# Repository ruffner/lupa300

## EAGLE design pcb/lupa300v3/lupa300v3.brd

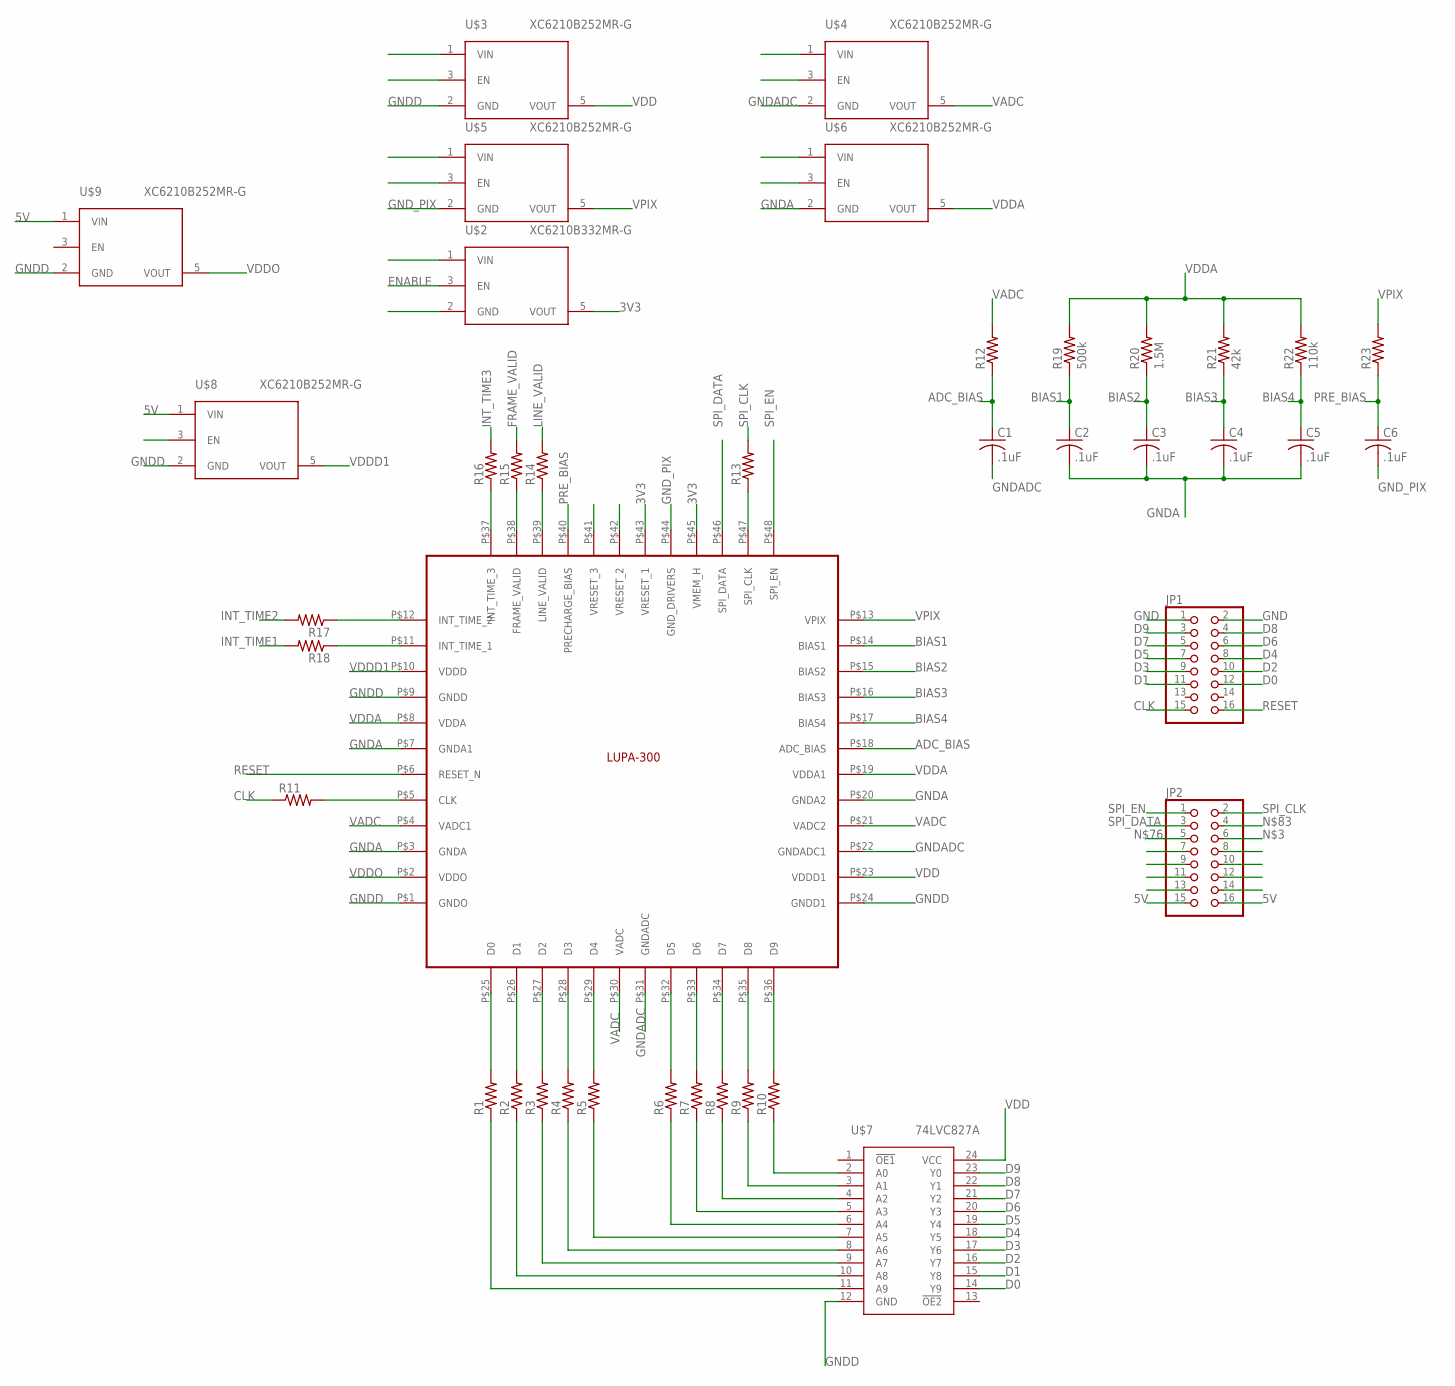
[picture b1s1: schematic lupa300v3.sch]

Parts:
C1, C2, C3, C4, C5, C6: .1uF; C0603K
JP1, JP2: PINHD-2X8; 2X08
R1, R2, R3, R4, R5, R6, R7, R8, R9, R10, R11, R12, R13, R14, R15, R16, R17, R18, R23: R-US_R0603; R0603
R19: 500k; R0603
R20: 1.5M; R0603
R21: 42k; R0603
R22: 110k; R0603
U$1: LUPA300
U$2: XC6210B332MR-G; SOT25
U$3, U$4, U$5, U$6, U$8, U$9: XC6210B252MR-G; SOT25
U$7: 74LVC827A; TSSOP24

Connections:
3V3: U$1.P$43 (VRESET_1), U$1.P$45 (VMEM_H), U$2.5 (VOUT)
5V: JP2.15, JP2.16, U$2.1 (VIN), U$3.1 (VIN), U$4.1 (VIN), U$5.1 (VIN), U$6.1 (VIN), U$8.1 (VIN), U$9.1 (VIN)
ADC_BIAS: C1.1, R12.1, U$1.P$18 (ADC_BIAS)
BIAS1: C2.1, R19.1, U$1.P$14 (BIAS1)
BIAS2: C3.1, R20.1, U$1.P$15 (BIAS2)
BIAS3: C4.1, R21.1, U$1.P$16 (BIAS3)
BIAS4: C5.1, R22.1, U$1.P$17 (BIAS4)
CLK: JP1.15, R11.1
D0: JP1.12, U$7.14 (Y9)
D1: JP1.11, U$7.15 (Y8)
D2: JP1.10, U$7.16 (Y7)
D3: JP1.9, U$7.17 (Y6)
D4: JP1.8, U$7.18 (Y5)
D5: JP1.7, U$7.19 (Y4)
D6: JP1.6, U$7.20 (Y3)
D7: JP1.5, U$7.21 (Y2)
D8: JP1.4, U$7.22 (Y1)
D9: JP1.3, U$7.23 (Y0)
ENABLE: U$2.3 (EN), U$3.3 (EN), U$4.3 (EN), U$5.3 (EN), U$6.3 (EN)
FRAME_VALID: R15.2
GND: JP1.1, JP1.2
GNDA: C2.2, C3.2, C4.2, C5.2, U$1.P$3 (GNDA), U$1.P$7 (GNDA1), U$1.P$20 (GNDA2), U$6.2 (GND)
GNDADC: C1.2, U$1.P$22 (GNDADC1), U$1.P$31 (GNDADC), U$4.2 (GND)
GNDD: U$1.P$1 (GNDO), U$1.P$9 (GNDD), U$1.P$24 (GNDD1), U$3.2 (GND), U$7.12 (GND), U$8.2 (GND), U$9.2 (GND)
GND_PIX: C6.2, U$1.P$44 (GND_DRIVERS), U$5.2 (GND)
INT1: R18.1, U$1.P$11 (INT_TIME_1)
INT2: R17.1, U$1.P$12 (INT_TIME_2)
INT_TIME1: R18.2
INT_TIME2: R17.2
INT_TIME3: R16.2
LINE_VALID: R14.2
unnamed: R1.2, U$1.P$25 (D0)
unnamed: R2.2, U$1.P$26 (D1)
unnamed: R3.2, U$1.P$27 (D2)
unnamed: R4.2, U$1.P$28 (D3)
unnamed: R5.2, U$1.P$29 (D4)
unnamed: R6.2, U$1.P$32 (D5)
unnamed: R7.2, U$1.P$33 (D6)
unnamed: R8.2, U$1.P$34 (D7)
unnamed: R9.2, U$1.P$35 (D8)
unnamed: R10.2, U$1.P$36 (D9)
unnamed: R11.2, U$1.P$5 (CLK)
unnamed: R13.1, U$1.P$47 (SPI_CLK)
unnamed: R14.1, U$1.P$39 (LINE_VALID)
unnamed: R15.1, U$1.P$38 (FRAME_VALID)
unnamed: R16.1, U$1.P$37 (INT_TIME_3)
unnamed: R10.1, U$7.2 (A0)
unnamed: R9.1, U$7.3 (A1)
unnamed: R8.1, U$7.4 (A2)
unnamed: R7.1, U$7.5 (A3)
unnamed: R6.1, U$7.6 (A4)
unnamed: R5.1, U$7.7 (A5)
unnamed: R4.1, U$7.8 (A6)
unnamed: R3.1, U$7.9 (A7)
unnamed: R2.1, U$7.10 (A8)
unnamed: R1.1, U$7.11 (A9)
PRE_BIAS: C6.1, R23.1, U$1.P$40 (PRECHARGE_BIAS)
RESET: JP1.16, U$1.P$6 (RESET_N)
SPI_CLK: JP2.2, R13.2
SPI_DATA: JP2.3, U$1.P$46 (SPI_DATA)
SPI_EN: JP2.1, U$1.P$48 (SPI_EN)
VADC: R12.2, U$1.P$4 (VADC1), U$1.P$21 (VADC2), U$1.P$30 (VADC), U$4.5 (VOUT)
VDD: U$1.P$23 (VDDD1), U$3.5 (VOUT), U$7.24 (VCC)
VDDA: R19.2, R20.2, R21.2, R22.2, U$1.P$8 (VDDA), U$1.P$19 (VDDA1), U$6.5 (VOUT)
VDDD1: U$1.P$10 (VDDD), U$8.5 (VOUT)
VDDO: U$1.P$2 (VDDO), U$9.5 (VOUT)
VPIX: R23.2, U$1.P$13 (VPIX), U$5.5 (VOUT)

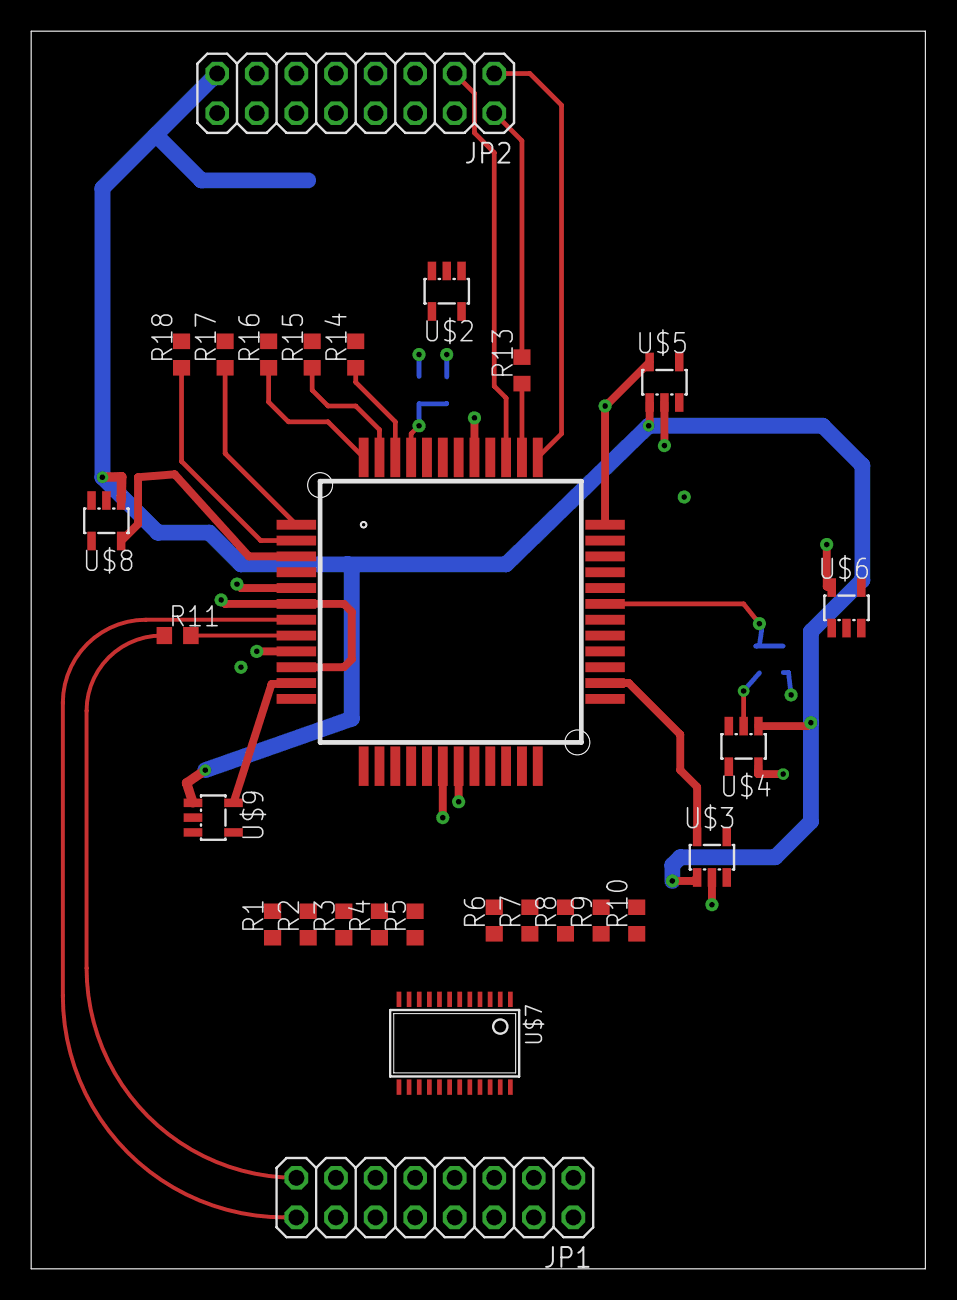
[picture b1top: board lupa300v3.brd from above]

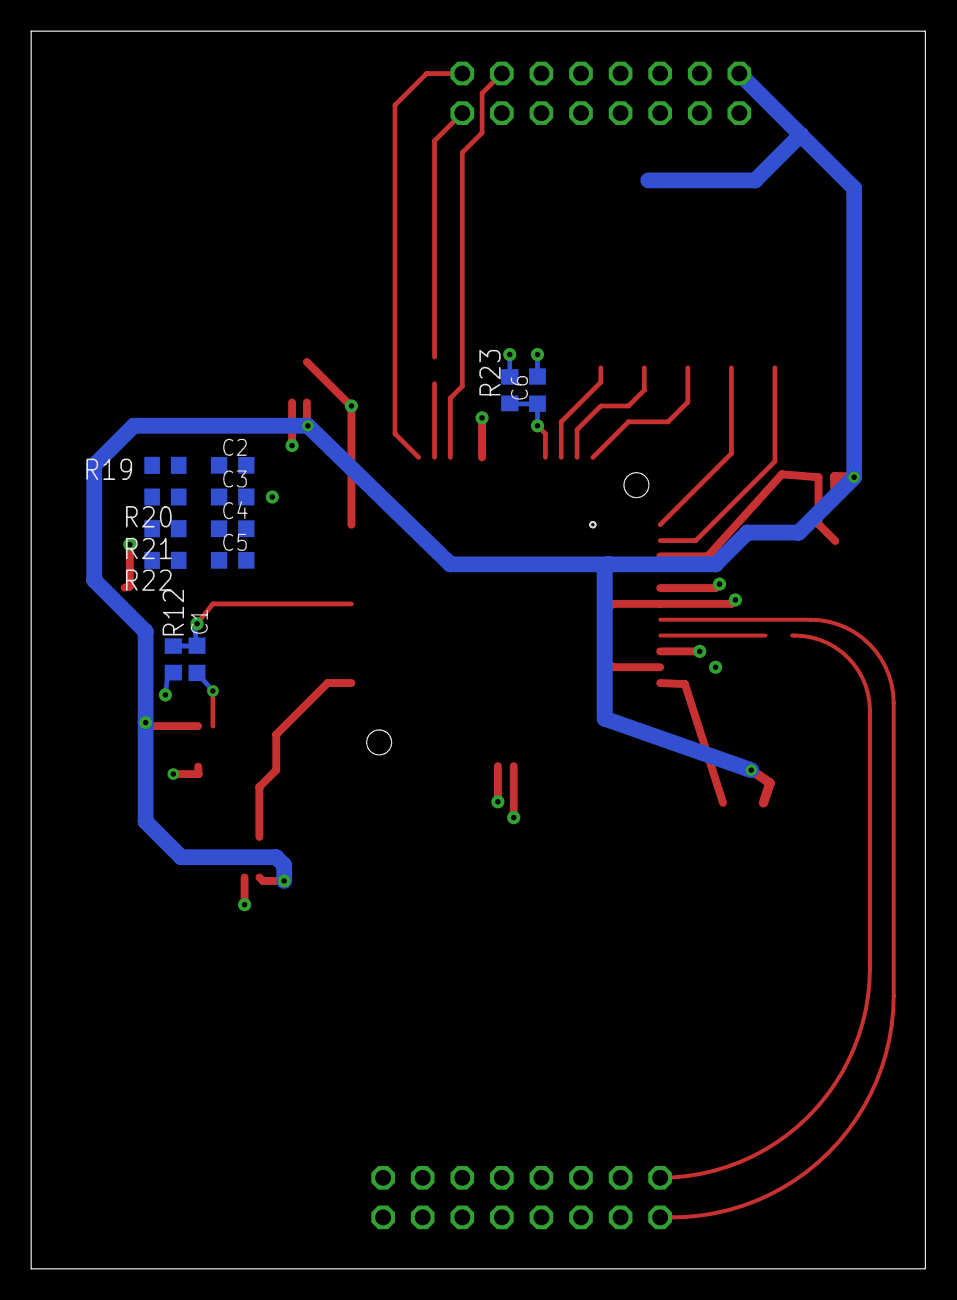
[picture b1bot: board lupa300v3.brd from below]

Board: 4 copper layers, 57.4 x 79.4 mm, 40 parts (12 on the bottom side), 62 nets.

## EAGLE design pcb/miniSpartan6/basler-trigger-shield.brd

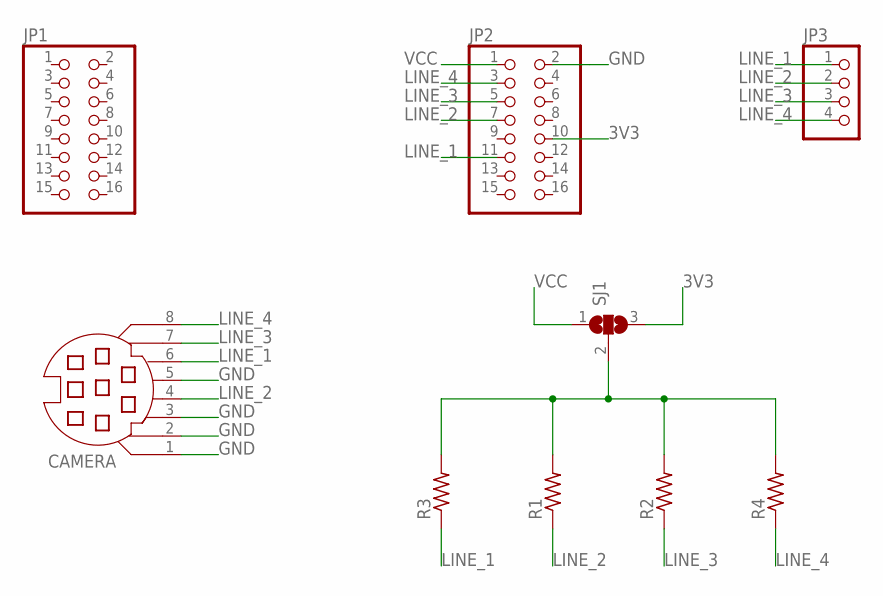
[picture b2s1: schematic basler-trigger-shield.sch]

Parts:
CAMERA: MD08SS; MDIN08SS
JP1, JP2: PINHD-2X8; 2X08
JP3: PINHD-1X4; 1X04
R1, R2, R3, R4: R-US_R0603; R0603
SJ1: SJ2W; SJ_2

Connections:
3V3: JP2.10, SJ1.3
GND: CAMERA.1, CAMERA.2, CAMERA.3, CAMERA.5, JP2.2
LINE_1: CAMERA.6, JP2.11, JP3.1, R3.1
LINE_2: CAMERA.4, JP2.7, JP3.2, R1.1
LINE_3: CAMERA.7, JP2.5, JP3.3, R2.1
LINE_4: CAMERA.8, JP2.3, JP3.4, R4.1
unnamed: R1.2, R2.2, R3.2, R4.2, SJ1.2
VCC: JP2.1, SJ1.1

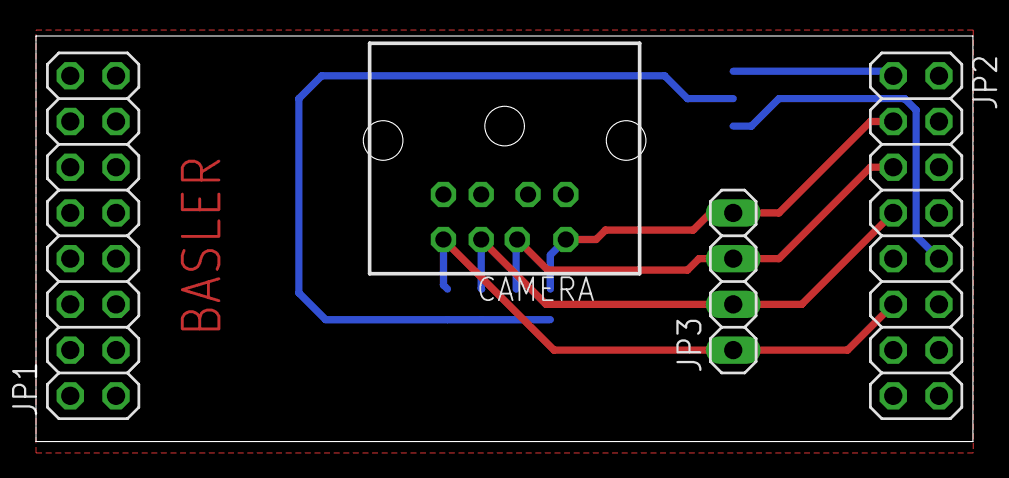
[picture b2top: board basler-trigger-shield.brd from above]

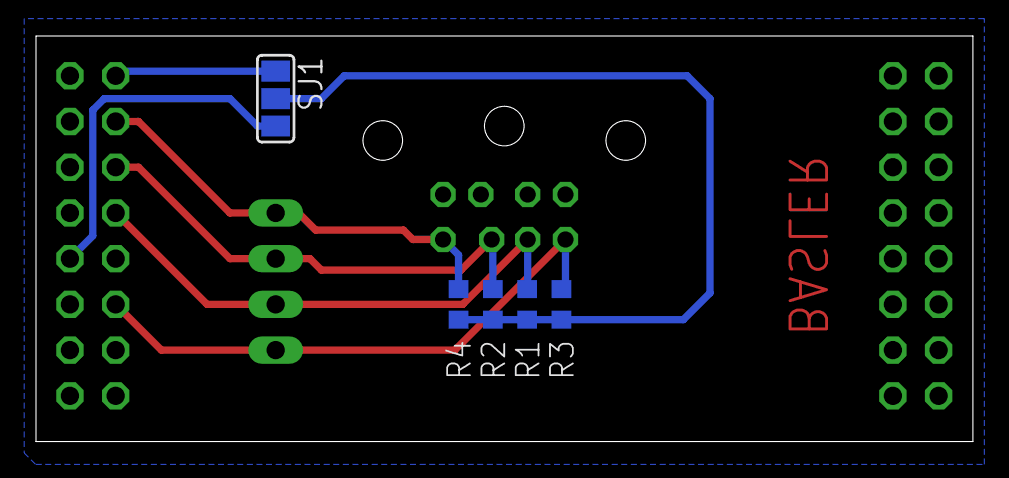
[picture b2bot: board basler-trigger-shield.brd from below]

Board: 2 copper layers, 52.0 x 22.5 mm, 9 parts (5 on the bottom side), 8 nets.

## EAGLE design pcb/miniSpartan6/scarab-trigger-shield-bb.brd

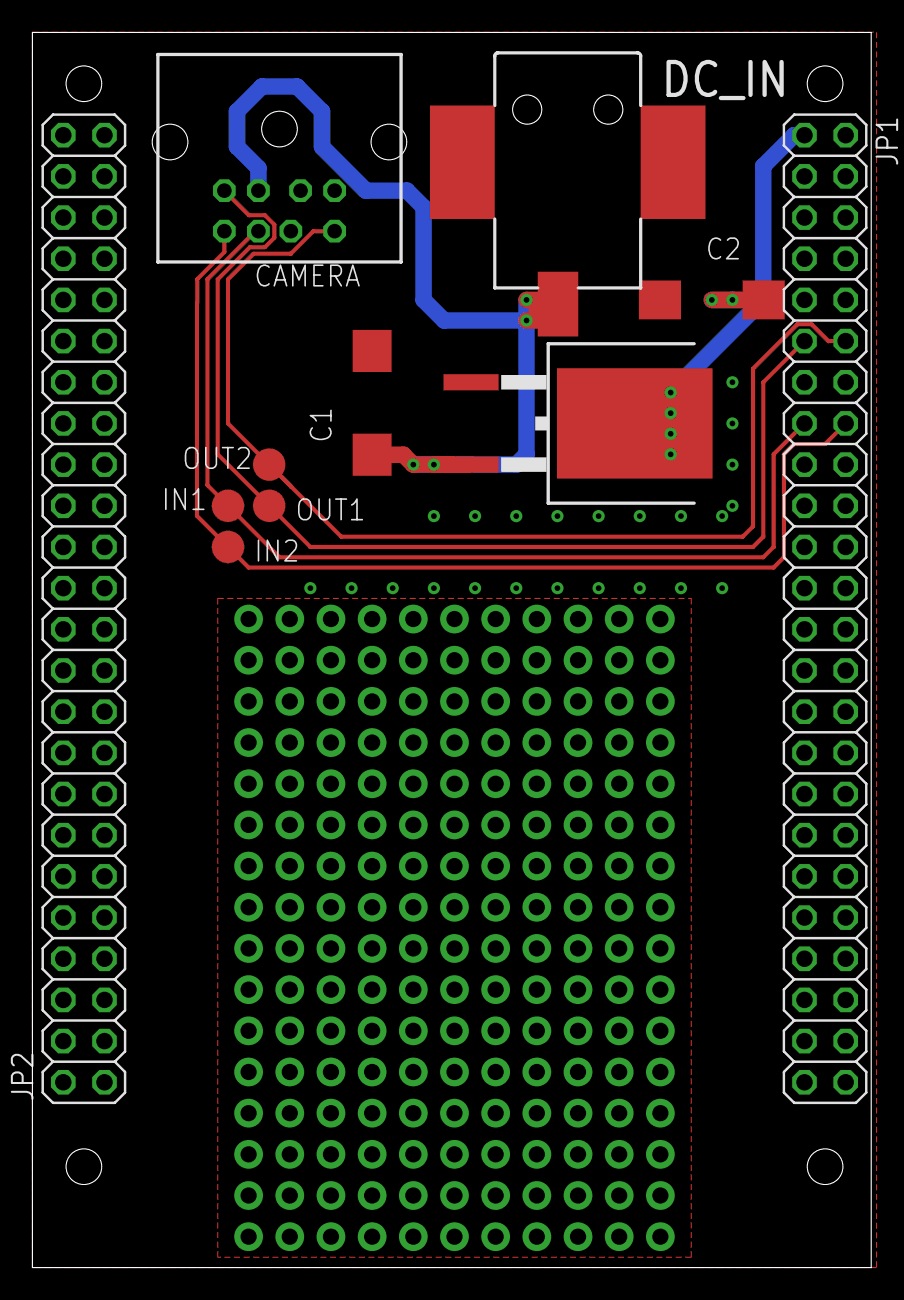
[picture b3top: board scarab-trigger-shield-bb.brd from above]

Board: 2 copper layers, 51.7 x 76.2 mm, 12 parts (0 on the bottom side), 7 nets.

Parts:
C1, C2: CT7343
CAMERA: MDIN08SS
DC_IN: 694106105102
IN1, IN2: TPTP20R; TP20R
JP1, JP2: 2X24
OUT1, OUT2: TPTP20R; TP20R
U$1: LM1085; TO263
U$2: 12X16PERF; PERF-GRID

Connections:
GND: C1.-, C2.-, CAMERA.2, CAMERA.7, DC_IN.2, DC_IN.3, JP1.2, U$1.1
SYNC_IN1: CAMERA.4, IN1.TP, JP1.15
SYNC_IN2: CAMERA.6, IN2.TP, JP1.16
SYNC_OUT1: CAMERA.3, JP1.11, OUT1.TP
SYNC_OUT2: CAMERA.8, JP1.12, OUT2.TP
VCC: C2.+, JP1.1, U$1.3
VIN: C1.+, CAMERA.1, DC_IN.1, U$1.2

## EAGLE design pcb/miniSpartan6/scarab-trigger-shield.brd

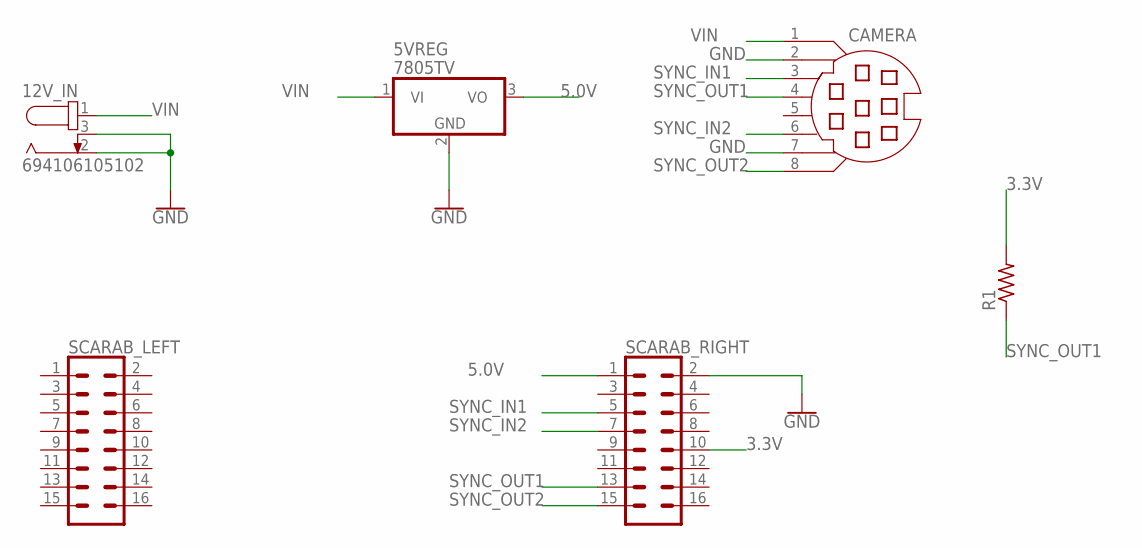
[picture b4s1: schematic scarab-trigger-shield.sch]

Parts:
5VREG: 7805TV; TO220V
12V_IN: 694106105102
CAMERA: MD08SS; MDIN08SS
R1: R-US_M1206; M1206
SCARAB_LEFT: CONN_08X2; 2X8
SCARAB_RIGHT: CONN_08X2; 2X8

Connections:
3.3V: R1.2, SCARAB_RIGHT.10
5.0V: 5VREG.3 (VO), SCARAB_RIGHT.1
GND: 5VREG.2 (GND), 12V_IN.2, 12V_IN.3, CAMERA.2, CAMERA.7, SCARAB_RIGHT.2
SYNC_IN1: CAMERA.3, SCARAB_RIGHT.5
SYNC_IN2: CAMERA.6, SCARAB_RIGHT.7
SYNC_OUT1: CAMERA.4, R1.1, SCARAB_RIGHT.13
SYNC_OUT2: CAMERA.8, SCARAB_RIGHT.15
VIN: 5VREG.1 (VI), 12V_IN.1, CAMERA.1

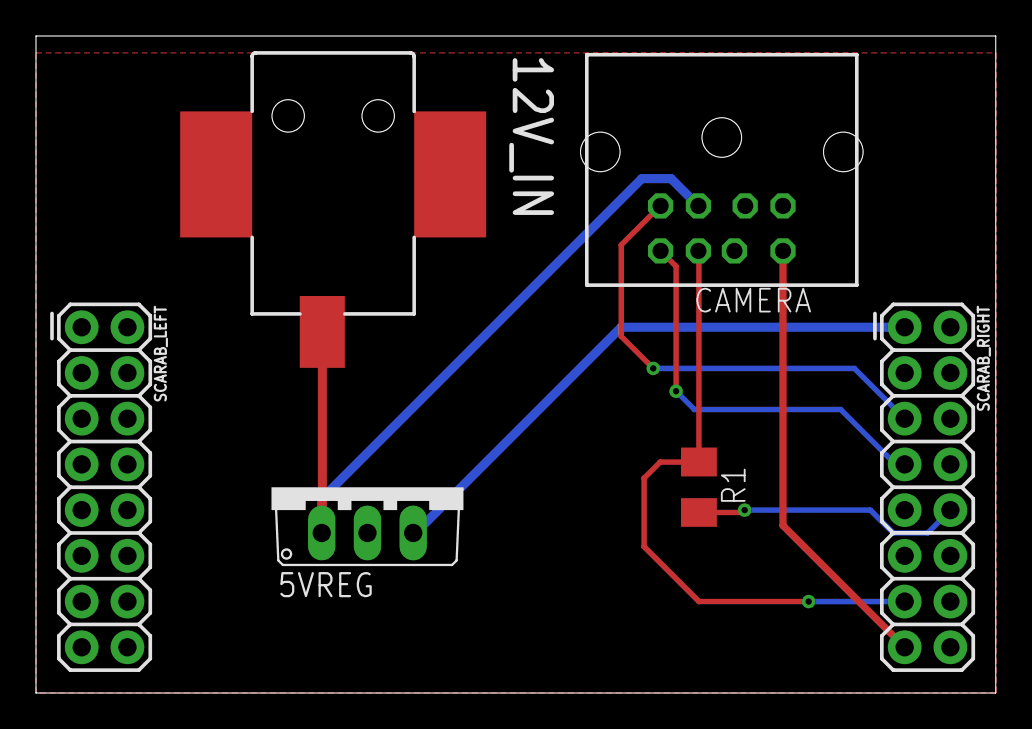
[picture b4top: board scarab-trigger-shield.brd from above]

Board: 2 copper layers, 53.3 x 36.5 mm, 6 parts (0 on the bottom side), 8 nets.

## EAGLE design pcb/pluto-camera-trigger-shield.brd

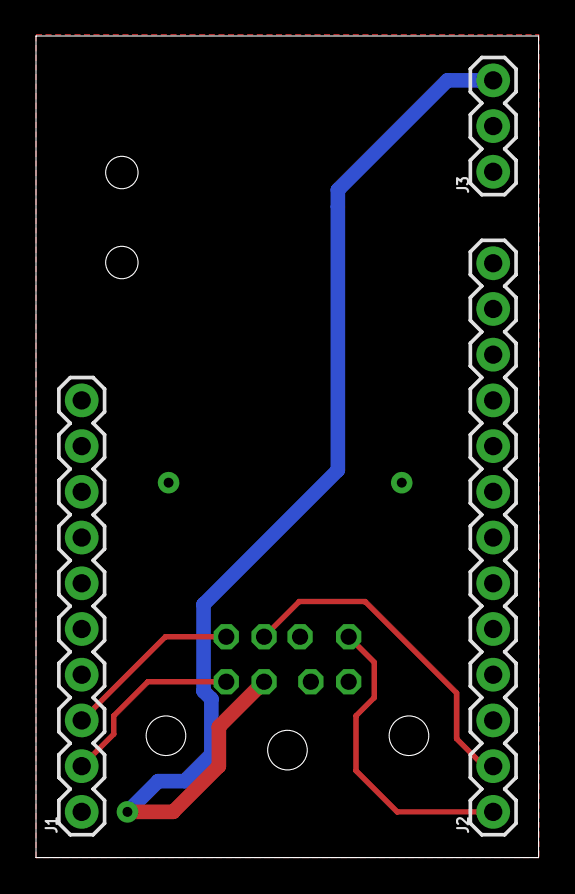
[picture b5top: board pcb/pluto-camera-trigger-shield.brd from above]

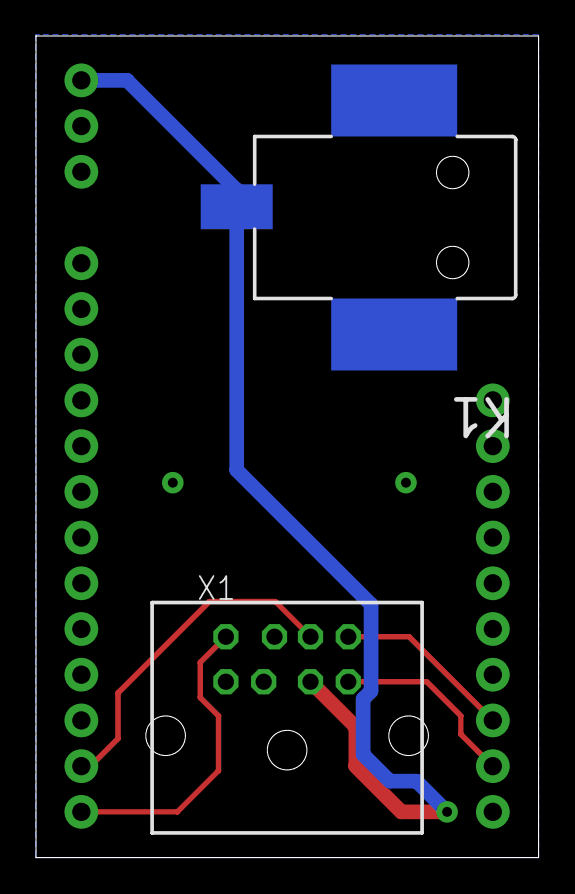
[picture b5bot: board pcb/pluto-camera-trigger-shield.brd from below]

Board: 2 copper layers, 27.9 x 45.6 mm, 5 parts (2 on the bottom side), 6 nets.

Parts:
J1: 1X10
J2: 1X13
J3: 455-1750-1-ND; 1X03
K1: 694106105102
X1: MDIN08SS

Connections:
GND: J1.1, J3.1, K1.2, K1.3, X1.2, X1.7
IO3: J2.1, X1.8
IO4: J2.2, X1.4
IO72: J1.3, X1.6
IO73: J1.2, X1.3
VIN: J3.3, K1.1, X1.1

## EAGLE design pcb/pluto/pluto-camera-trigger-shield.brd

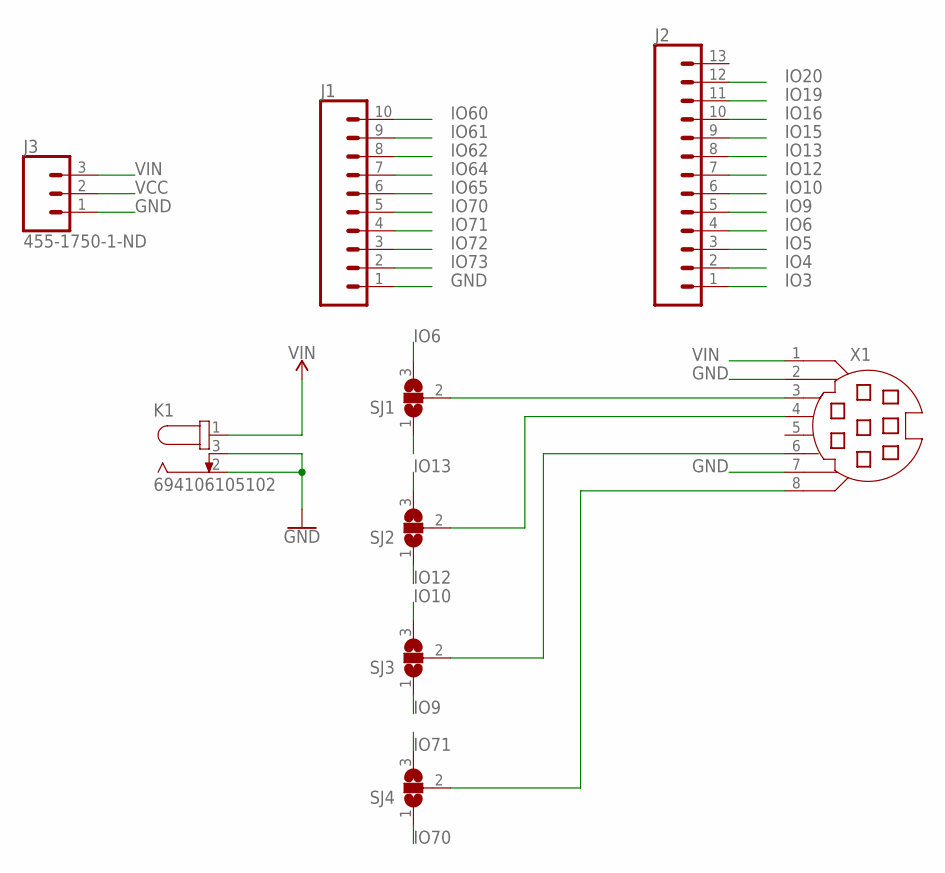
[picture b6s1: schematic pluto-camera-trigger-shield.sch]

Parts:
J1: CONN_10"; 1X10
J2: CONN_13; 1X13
J3: 455-1750-1-ND; 1X03
K1: 694106105102
SJ1, SJ2, SJ3, SJ4: SJ2W; SJ_2
X1: MD08SS; MDIN08SS

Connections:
GND: J1.1, J3.1, K1.2, K1.3, X1.2, X1.7
IO3: J2.1
IO4: J2.2
IO5: J2.3, SJ1.1
IO6: J2.4, SJ1.3
IO9: J2.5, SJ3.1
IO10: J2.6, SJ3.3
IO12: J2.7, SJ2.1
IO13: J2.8, SJ2.3
IO15: J2.9
IO16: J2.10
IO19: J2.11
IO20: J2.12
IO60: J1.10
IO61: J1.9
IO62: J1.8
IO64: J1.7
IO65: J1.6
IO70: J1.5, SJ4.1
IO71: J1.4, SJ4.3
IO72: J1.3
IO73: J1.2
unnamed: SJ1.2, X1.3
unnamed: SJ2.2, X1.4
unnamed: SJ3.2, X1.6
unnamed: SJ4.2, X1.8
VCC: J3.2
VIN: J3.3, K1.1, X1.1

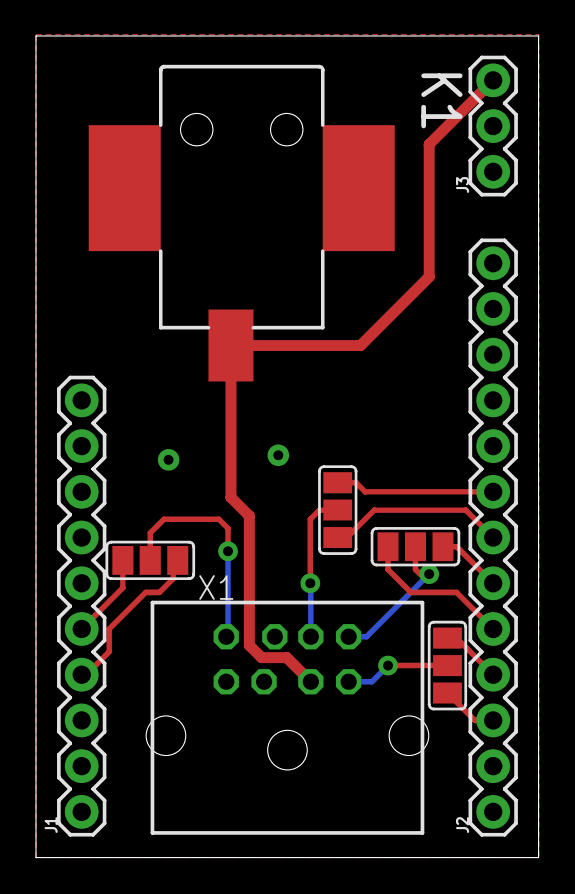
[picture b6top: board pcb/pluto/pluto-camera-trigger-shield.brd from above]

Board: 2 copper layers, 27.9 x 45.6 mm, 9 parts (0 on the bottom side), 14 nets.

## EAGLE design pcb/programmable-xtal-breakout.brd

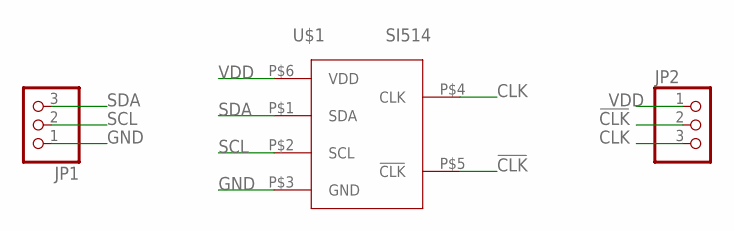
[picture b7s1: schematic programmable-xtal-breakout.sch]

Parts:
JP1, JP2: PINHD-1X3; 1X03
U$1: SI514; XTAL-6PIN

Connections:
!CLK: JP2.2, U$1.P$5 (!CLK)
CLK: JP2.3, U$1.P$4 (CLK)
GND: JP1.1, U$1.P$3 (GND)
SCL: JP1.2, U$1.P$2 (SCL)
SDA: JP1.3, U$1.P$1 (SDA)
VDD: JP2.1, U$1.P$6 (VDD)

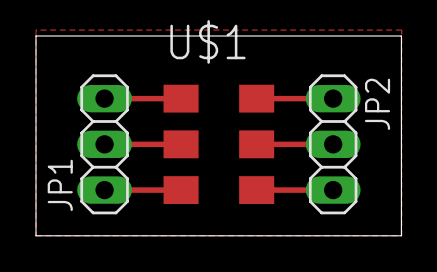
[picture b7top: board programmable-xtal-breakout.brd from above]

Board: 2 copper layers, 20.3 x 11.1 mm, 3 parts (0 on the bottom side), 6 nets.

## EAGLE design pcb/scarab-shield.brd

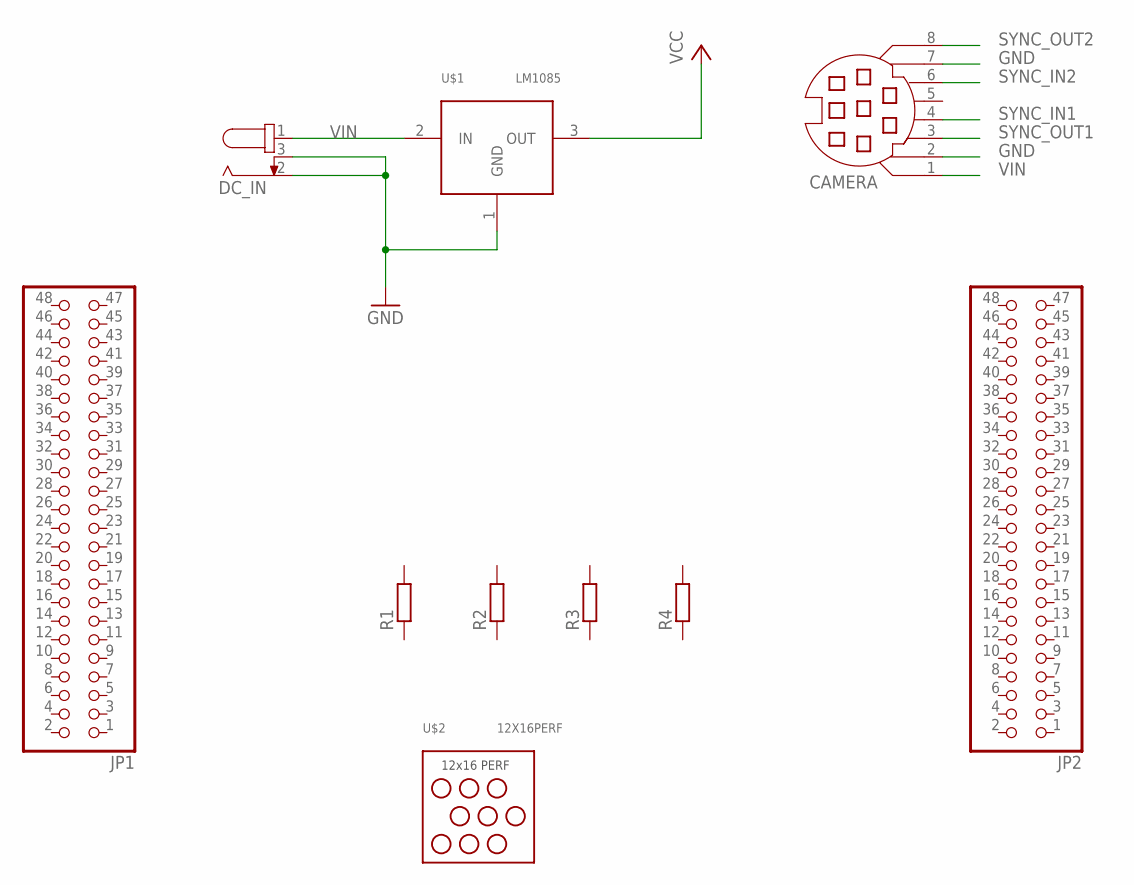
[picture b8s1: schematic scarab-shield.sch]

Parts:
CAMERA: MD08SS; MDIN08SS
DC_IN: 694106105102
JP1, JP2: PINHD-2X24; 2X24
R1, R2, R3, R4: R-EU_M1206; M1206
U$1: LM1085; TO263
U$2: 12X16PERF; PERF-GRID

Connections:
GND: CAMERA.2, CAMERA.7, DC_IN.2, DC_IN.3, U$1.1 (GND)
SYNC_IN1: CAMERA.4
SYNC_IN2: CAMERA.6
SYNC_OUT1: CAMERA.3
SYNC_OUT2: CAMERA.8
VCC: U$1.3 (OUT)
VIN: CAMERA.1, DC_IN.1, U$1.2 (IN)

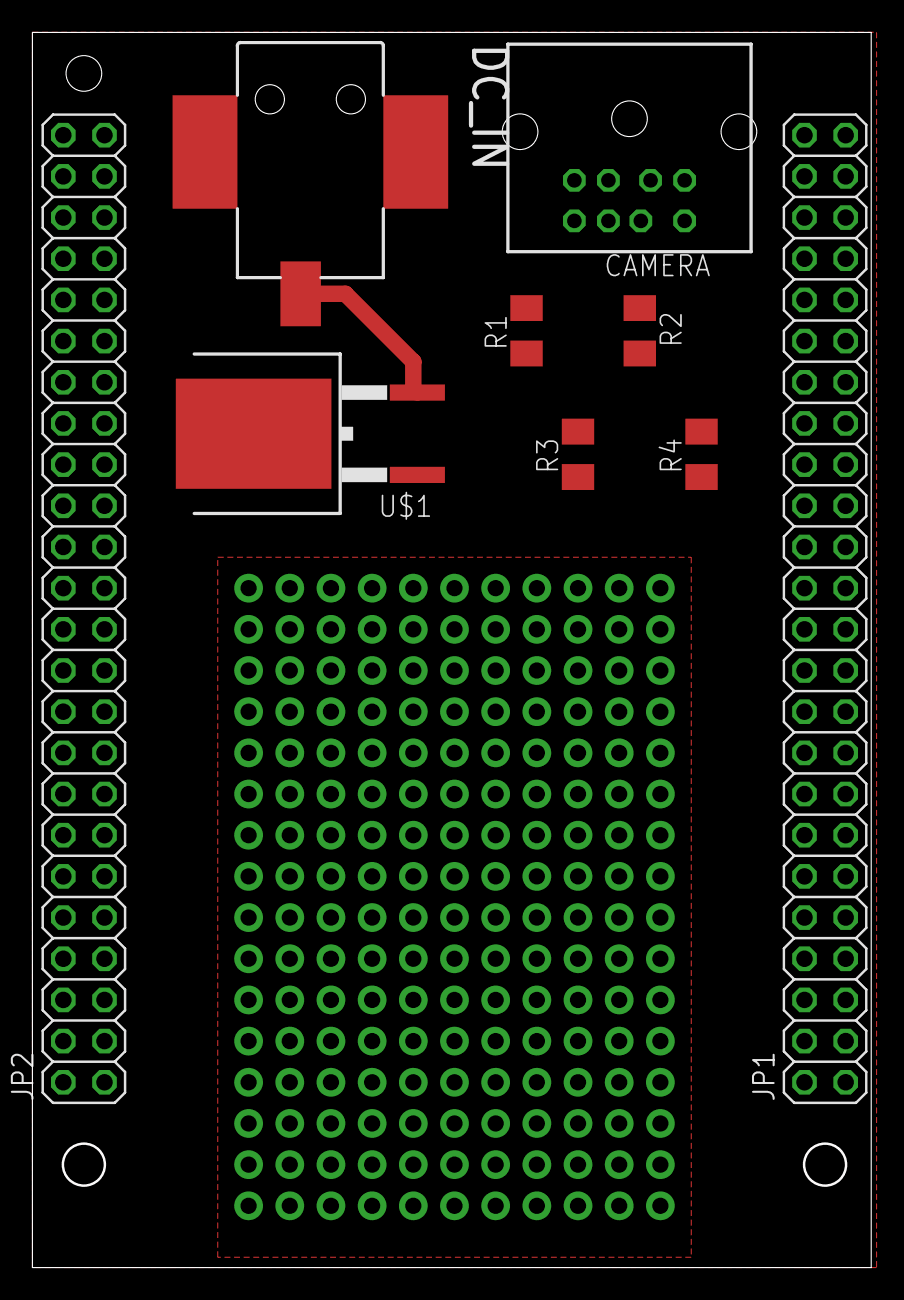
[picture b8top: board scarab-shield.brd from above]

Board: 2 copper layers, 51.7 x 76.2 mm, 10 parts (0 on the bottom side), 2 nets.

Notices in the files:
parts and their libraries:
Wurth_Elektronik_Electromechanic_DC_Powe: Copyright: Würth Elektronik
SparkFun-Connectors: Licensing: Creative Commons ShareAlike 4.0 International - https://creativecommons.org/licenses/by-sa/4.0
